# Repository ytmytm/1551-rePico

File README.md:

# 1551-rePico

Commodore **1551** disk-drive replacement for **Plus/4 / C16 / C116**, based on a [Raspberry Pi Pico 2](https://www.raspberrypi.com/products/raspberry-pi-pico-2/) (RP2350, **non-wireless** — raspberry logo on the soldermask; not Pico 2 W). Firmware and GCR/SD logic are derived from [1541-rePico](https://github.com/fook42/1541-rePico) / [1541-rebuild](https://github.com/ThKattanek/1541-rebuild).

## What this is

A self-contained **drive computer** — **Pico 2** + **6510T** (or [MOS CPU Replacer](https://github.com/monotech/MOS_CPU_Replacer)) + XC9572XL CPLD + RAM + ROM — that replaces the Pi1551-III mainboard (Raspberry Pi 3 + TCBM). It reuses the Pi1551-III **mechanical stack**: front panel, top/bottom faceplates, and overall assembly. BOM, Gerbers, and build notes for those parts stay in the [Pi1551-III](https://github.com/ytmytm/Pi1551-III) repository.

The finished device connects to the computer through a ribbon cable to **[plus4-tcbm2sd](https://github.com/ytmytm/plus4-tcbm2sd)** — same as Pi1551-III.

In short: same case and front panel as Pi1551-III; this repo supplies the Pico 2 / 6510T mainboard, CPLD bitstream, DOS ROMs, and firmware.

### Repository layout

| Path | Role |
|------|------|
| `firmware-1551-III-pico/` | **Supported** firmware |
| `hardware-1551-III-Pico/` | **Supported** KiCad mainboard |
| `hdl-1551-III/` | **Supported** CPLD (`Fake6523`) |
| `roms/` | **Supported** 1551 DOS images for the 27C512 (see [`roms/README.md`](roms/README.md)) |
| `no-OS-FatFS-SD-SDIO-SPI-RPi-Pico/` | Shared FatFs/SD submodule |
| `tools/` | Optional host helper (`conv_x64` D64↔G64); see [`tools/README.md`](tools/README.md) |
| `experimental/` | **Archival only** — early plug-over-1551 daughterboard + old firmware (see [`experimental/README.md`](experimental/README.md)) |

### Compared to a stock 1551

| Stock 1551 | This board |
|------------|------------|
| **6510T** CPU | Same **6510T**, or a [MOS CPU Replacer](https://github.com/monotech/MOS_CPU_Replacer) in that socket |
| ~2 KB SRAM | **32 KB** SRAM (`KM62256`) with a **1551-RAMBoard-style** map: `$0000–$3FFF` + `$8000–$9FFF` (extra RAM window; decode in the CPLD) |
| ~16 KB ROM | **64 KB** EPROM (`27C512`): two **32 KB** DOS images, selected by jumper **J2** — burn a [1551-RAMBOard](https://github.com/ytmytm/1551-RAMBOard) 64K image from [`roms/`](roms/) |
| Device #8 / #9 (hardware strap) | Jumper / strap for **device 8 or 9** (same idea as stock) |
| **6523** TPI + discrete address decode | **XC9572XL CPLD** (`hdl-1551-III/` Fake6523): TPI replacement **and** RAM/ROM chip-select decode |
| 2 MHz crystal (Phi0) | **Pico 2** generates **2 MHz Phi0** (PWM) |
| ~100 Hz IRQ oscillator | **Pico 2** generates **100 Hz IRQ** (PWM) |
| Analog floppy + mech | **Pico 2** emulates the analog path and runs the UI |

### Pico 2 on this board

- **Phi0** and **IRQ** as in the table above — those clocks take dedicated GPIOs that a stock gate-array / discrete oscillator would otherwise free up
- Supplies **3.3 V** for the CPLD (and other 3.3 V rails on this board)
- Front-panel **UI**: OLED (I2C), plus rotary encoder, Back/Insert, SD card-detect, and DS0/DS1 via a **74HCT165** (same panel as Pi1551-III). The '165 is needed because after clock, IRQ, floppy bus, SPI SD, and I2C there were not enough GPIOs for every panel line directly
- **SD card**: FatFs images, browser UI, **card-detect hotplug**
- Floppy **datastream**: GCR to/from the “head”, **BYTE_READY** / related timing
- **Stepper**, optional **density** from DS0/DS1, **WPS** / disk-change toward DOS, activity LED

### CPLD role (short)

Bidirectional **ports** (TCBM on A, head data on B, handshake / MODE / DEVNUM / SYNC on C) are based on [ZXByteman/Fake6523](https://github.com/ZXByteman/Fake6523). The same chip is also **logic glue**:

- RAMBOard-style **address decode** (`/RAMSEL`, `/RAMOE`, `/ROMSEL`, TPI `/CS`), all **PHI2-qualified**
- **`XR/~W`** for SRAM `/WE` (qualified with PHI2)
- **`byte_latched`**: Pico 2 strobes `byte_ready_3v3`; the CPLD latches on the falling edge; any CPU access to the TPI window (`$4000–$7FFF`, e.g. DOS `BIT $4000`) clears the latch — the classic floppy byte-ready behaviour from 1541/1571 service docs, without a dedicated 1551 manual

## What you can do with it

- Mount **D64**, **G64**, and **PRG** images from an SD card (PRG is wrapped on the fly into a temporary D64). Format notes: [D64](doc/D64.TXT), [G64](doc/G64.TXT); optional PC conversion with [`tools/conv_x64`](tools/)
- Browse and mount images from the **OLED + encoder** front panel (Back / Insert), with **SD hotplug** when the socket has a card-detect switch
- Run as device **#8 or #9** on the Plus/4 TCBM bus via **[plus4-tcbm2sd](https://github.com/ytmytm/plus4-tcbm2sd)**
- Use **[1551-RAMBOard](https://github.com/ytmytm/1551-RAMBOard)** patched DOS in the 27C512 so track-cache / HypaRAM-style fastloaders work
- Prefer **[Parobek](https://github.com/ytmytm/plus4-parobek)** as the host utility ROM: it autodetects the RAMBOard DOS patch and provides a fastloader. For now we use Parobek’s **DirectoryBrowser** on the computer; `firmware-1551-III-pico/SoftwareC16/db12b.prg` is kept for a future on-device Load Selector (**TODO**)

## Build and assemble

### 1. Clone (with submodules)

The FatFs/SD driver is a **git submodule**. Without it, CMake will fail.

```bash
git clone --recurse-submodules https://github.com/ytmytm/1551-rePico.git
cd 1551-rePico
```

If you already cloned without submodules:

```bash
git submodule update --init --recursive
```

You need at least `no-OS-FatFS-SD-SDIO-SPI-RPi-Pico/` for the supported firmware.

### 2. Host packages

**Linux (Debian-like):**

```bash
sudo apt install cmake ninja-build libusb-1.0-0-dev build-essential \
  pkg-config python3 xxd gcc-arm-none-eabi \
  libnewlib-arm-none-eabi libstdc++-arm-none-eabi-newlib
```

**macOS (Homebrew):**

```bash
brew install cmake ninja libusb pkg-config python3
brew install --cask gcc-arm-embedded
```

`xxd` is usually already on macOS (Xcode Command Line Tools). Ensure `arm-none-eabi-gcc` is on your `PATH`.

### 3. Raspberry Pi Pico SDK

From [pico-sdk](https://github.com/raspberrypi/pico-sdk):

```bash
git clone https://github.com/raspberrypi/pico-sdk.git
cd pico-sdk
git submodule update --init lib/mbedtls
export PICO_SDK_PATH="$(pwd)"
echo "export PICO_SDK_PATH=$PICO_SDK_PATH" >> ~/.profile
```

Open a new shell (or `source ~/.profile`) so `PICO_SDK_PATH` is set. The Raspberry Pi Pico VS Code extension / `.pico-sdk` can provide the SDK instead.

### 4. picotool

From [picotool](https://github.com/raspberrypi/picotool): clone and build/install as in its README / BUILDING.md so `picotool` is on your `PATH`.

### 5. Compile firmware

```bash
cd firmware-1551-III-pico
mkdir -p build && cd build
cmake -G Ninja -DCMAKE_BUILD_TYPE=Release ..
ninja
```

Outputs include `1551-III-Pico.uf2` and `1551-III-Pico.elf`.

### 6. Flash the Pico 2

```bash
picotool load -t uf2 1551-III-Pico.uf2 -x -f
```

`-f` forces BOOTSEL when the app is running; `-x` starts the new firmware after load.

### 7. Main PCB (order / solder)

KiCad project: [`hardware-1551-III-Pico/`](hardware-1551-III-Pico/) (see its [`README.md`](hardware-1551-III-Pico/README.md)).

- Schematic PDF: [`plots/1551-III-Pico.pdf`](hardware-1551-III-Pico/plots/1551-III-Pico.pdf)
- Gerbers / drills: [`plots/`](hardware-1551-III-Pico/plots/)
- Fab pack: [`production/1551-III_Pico_2b.zip`](hardware-1551-III-Pico/production/1551-III_Pico_2b.zip)
- BOM / pick-and-place: [`production/bom.csv`](hardware-1551-III-Pico/production/bom.csv), [`positions.csv`](hardware-1551-III-Pico/production/positions.csv), [`designators.csv`](hardware-1551-III-Pico/production/designators.csv)
- **JP1–JP3**: leave default **1–2** (Pico 2 ↔ `74HCT165`). Alternate wiring was only insurance if the shift register failed — do not change them.

### 8. Program the CPLD

Flash [`hdl-1551-III/Fake6523.jed`](hdl-1551-III/Fake6523.jed) into the XC9572XL. The `.jed` was built with [Xilinx ISE 14.7](https://www.xilinx.com/support/download/index.html/content/xilinx/en/downloadNav/vivado-design-tools/archive-ise.html) (sources in `hdl-1551-III/`). Rebuild and JTAG steps (a Raspberry Pi 3 and jumper wires are enough) are in [plus4-tcbm2sd → CPLD firmware](https://github.com/ytmytm/plus4-tcbm2sd/blob/main/HardwareFirmware.md#cpld-firmware); the procedure is the same for this board.

### 9. Burn the DOS ROM

Program a 64K image from [`roms/`](roms/) into the 27C512 (see [`roms/README.md`](roms/README.md)). Prefer a [1551-RAMBOard](https://github.com/ytmytm/1551-RAMBOard) image; jumper **J2** selects the active 32K half (use the patched upper bank).

### 10. Panel, case, and host link

- Front panel / faceplates / mechanical assembly: **[Pi1551-III](https://github.com/ytmytm/Pi1551-III)**
- Host: **[plus4-tcbm2sd](https://github.com/ytmytm/plus4-tcbm2sd)** + ribbon cable

## History and relation to 1541-rePico

This is a **separate product**, not a fork kept in sync with upstream 1541-rePico: a real **6510T** + CPLD 1551 path in a [Pi1551-III](https://github.com/ytmytm/Pi1551-III) enclosure. Useful upstream changes may still be cherry-picked by hand.

**Starting point.** Take 1541-rePico’s GCR/SD/UI core and aim at a **1551** for Plus/4 that still fits **Pi1551-III** and talks through **tcbm2sd**, so the Pi 3 Module-rotated board becomes a Pico 2 + real 6510T path.

**Daughterboard bring-up** (now `experimental/`). First hardware plugged over a stock 1551 mainboard: reuse CPU/TPI/RAM/ROM, Pico 2 for the analog path, Fake6523 in the CPLD. That proved TCBM/GCR, pin maps, and design rules: Phi0 and 100 Hz IRQ from the Pico 2 (gate array optional), `XR/~W` in the CPLD, PHI2-qualified chip-selects (otherwise RAM bus contention), `byte_latched` as classic byte-ready, and slower zone-0 timing than 1541 defaults. Once the motherboard was only a RAM/ROM carrier, a self-contained board was the next step.

**1551-III-Pico.** Decode moved into the CPLD (no discrete `'139`/`'00`), RAMBOard map and 64K DOS images, Pi1551-III panel (SH1106 + 74HCT165). Firmware lives in `firmware-1551-III-pico/`. Upstream 1541-rePico is not merged as a whole — only occasional hand cherry-picks.

| Mostly from 1541-rePico | Mostly new for 1551 / this board |
|-------------------------|----------------------------------|
| GCR encode/decode, track buffers, D64/G64 path | KiCad III board, CPLD glue + Fake6523 ports, RAMBOard decode |
| FatFs / SD wiring, much of the menu framework | Pico 2 as Phi0 + 100 Hz IRQ; '165 panel inputs |
| Build/flash with pico-sdk / picotool | TCBM via tcbm2sd; Parobek + patched DOS ROMs |
| | Zone-0 timing, byte-ready latch model, SD hotplug, III pinout |

### Credits

- [1541-rebuild](https://github.com/ThKattanek/1541-rebuild) — Thorsten Kattanek  
- [1541-rePico](https://github.com/fook42/1541-rePico) — fook42 (GCR/SD/UI lineage)  
- C64 image selector in upstream 1541-rePico — Peiselulli  
- Dev-container / debug docs on upstream — [BensonRSI](https://github.com/BensonRSI)  
- [Fake6523](https://github.com/ZXByteman/Fake6523) — ZXByteman / go4retro  
- [Pi1551-III](https://github.com/ytmytm/Pi1551-III), [plus4-tcbm2sd](https://github.com/ytmytm/plus4-tcbm2sd), [1551-RAMBOard](https://github.com/ytmytm/1551-RAMBOard), [plus4-parobek](https://github.com/ytmytm/plus4-parobek)

## Links

- Disk image formats overview: <https://ist.uwaterloo.ca/~schepers/formats.html>
- forum64 thread behind 1541-rebuild / 1541-rePico: <https://www.forum64.de/index.php?thread/59884-laufwerk-der-1541-emulieren>

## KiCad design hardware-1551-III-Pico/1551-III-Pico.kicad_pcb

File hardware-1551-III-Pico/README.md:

# 1551-III-Pico mainboard

KiCad project for the **horizontal main module** of [1551-rePico](../README.md): Pico2 + 6510T (or [MOS CPU Replacer](https://github.com/monotech/MOS_CPU_Replacer)) + XC9572XL CPLD + 32 KB SRAM + 64 KB EPROM. It replaces the Pi1551-III **Module-rotated** board and mates with the [Pi1551-III](https://github.com/ytmytm/Pi1551-III) front panel and faceplates.

Host connection is a ribbon cable to **[plus4-tcbm2sd](https://github.com/ytmytm/plus4-tcbm2sd)** (same as Pi1551-III).

## Design files

| Artifact | Path |
|----------|------|
| KiCad project | this folder (`1551-III-Pico.kicad_pro`) |
| Schematic PDF | [`plots/1551-III-Pico.pdf`](plots/1551-III-Pico.pdf) |
| Gerbers / drills | [`plots/`](plots/) |
| JLCPCB-style fab pack | [`production/1551-III_Pico_2b.zip`](production/1551-III_Pico_2b.zip) |
| BOM / positions | [`production/bom.csv`](production/bom.csv), [`production/positions.csv`](production/positions.csv), [`production/designators.csv`](production/designators.csv) |

## Related firmware / CPLD / ROMs

- Firmware: [`../firmware-1551-III-pico/`](../firmware-1551-III-pico/)
- CPLD bitstream: [`../hdl-1551-III/Fake6523.jed`](../hdl-1551-III/Fake6523.jed) — flash notes in the [top-level README](../README.md#8-program-the-cpld)
- DOS EPROM images (27C512): [`../roms/`](../roms/) — see [1551-RAMBOard](https://github.com/ytmytm/1551-RAMBOard) for provenance and patch details
- Mechanical / panel BOM: **[Pi1551-III](https://github.com/ytmytm/Pi1551-III)**

## Notes

- Internal bring-up / review notes: [`notes.txt`](notes.txt), [`hardware-review.md`](hardware-review.md)
- ROM bank select on this board is jumper **J2** (two 32 KB halves of the 27C512). Prefer a [1551-RAMBOard](https://github.com/ytmytm/1551-RAMBOard) 64K image so the upper half is the RAM-expansion / fastloader patch.
- **JP1–JP3** (GPIO26–28 ↔ `74HCT165`): leave as shipped / default **1–2**. They were only a fallback so the Pico could talk to the front-panel encoder directly if the shift register failed; '165 works and current firmware expects that path — do not rewire them.

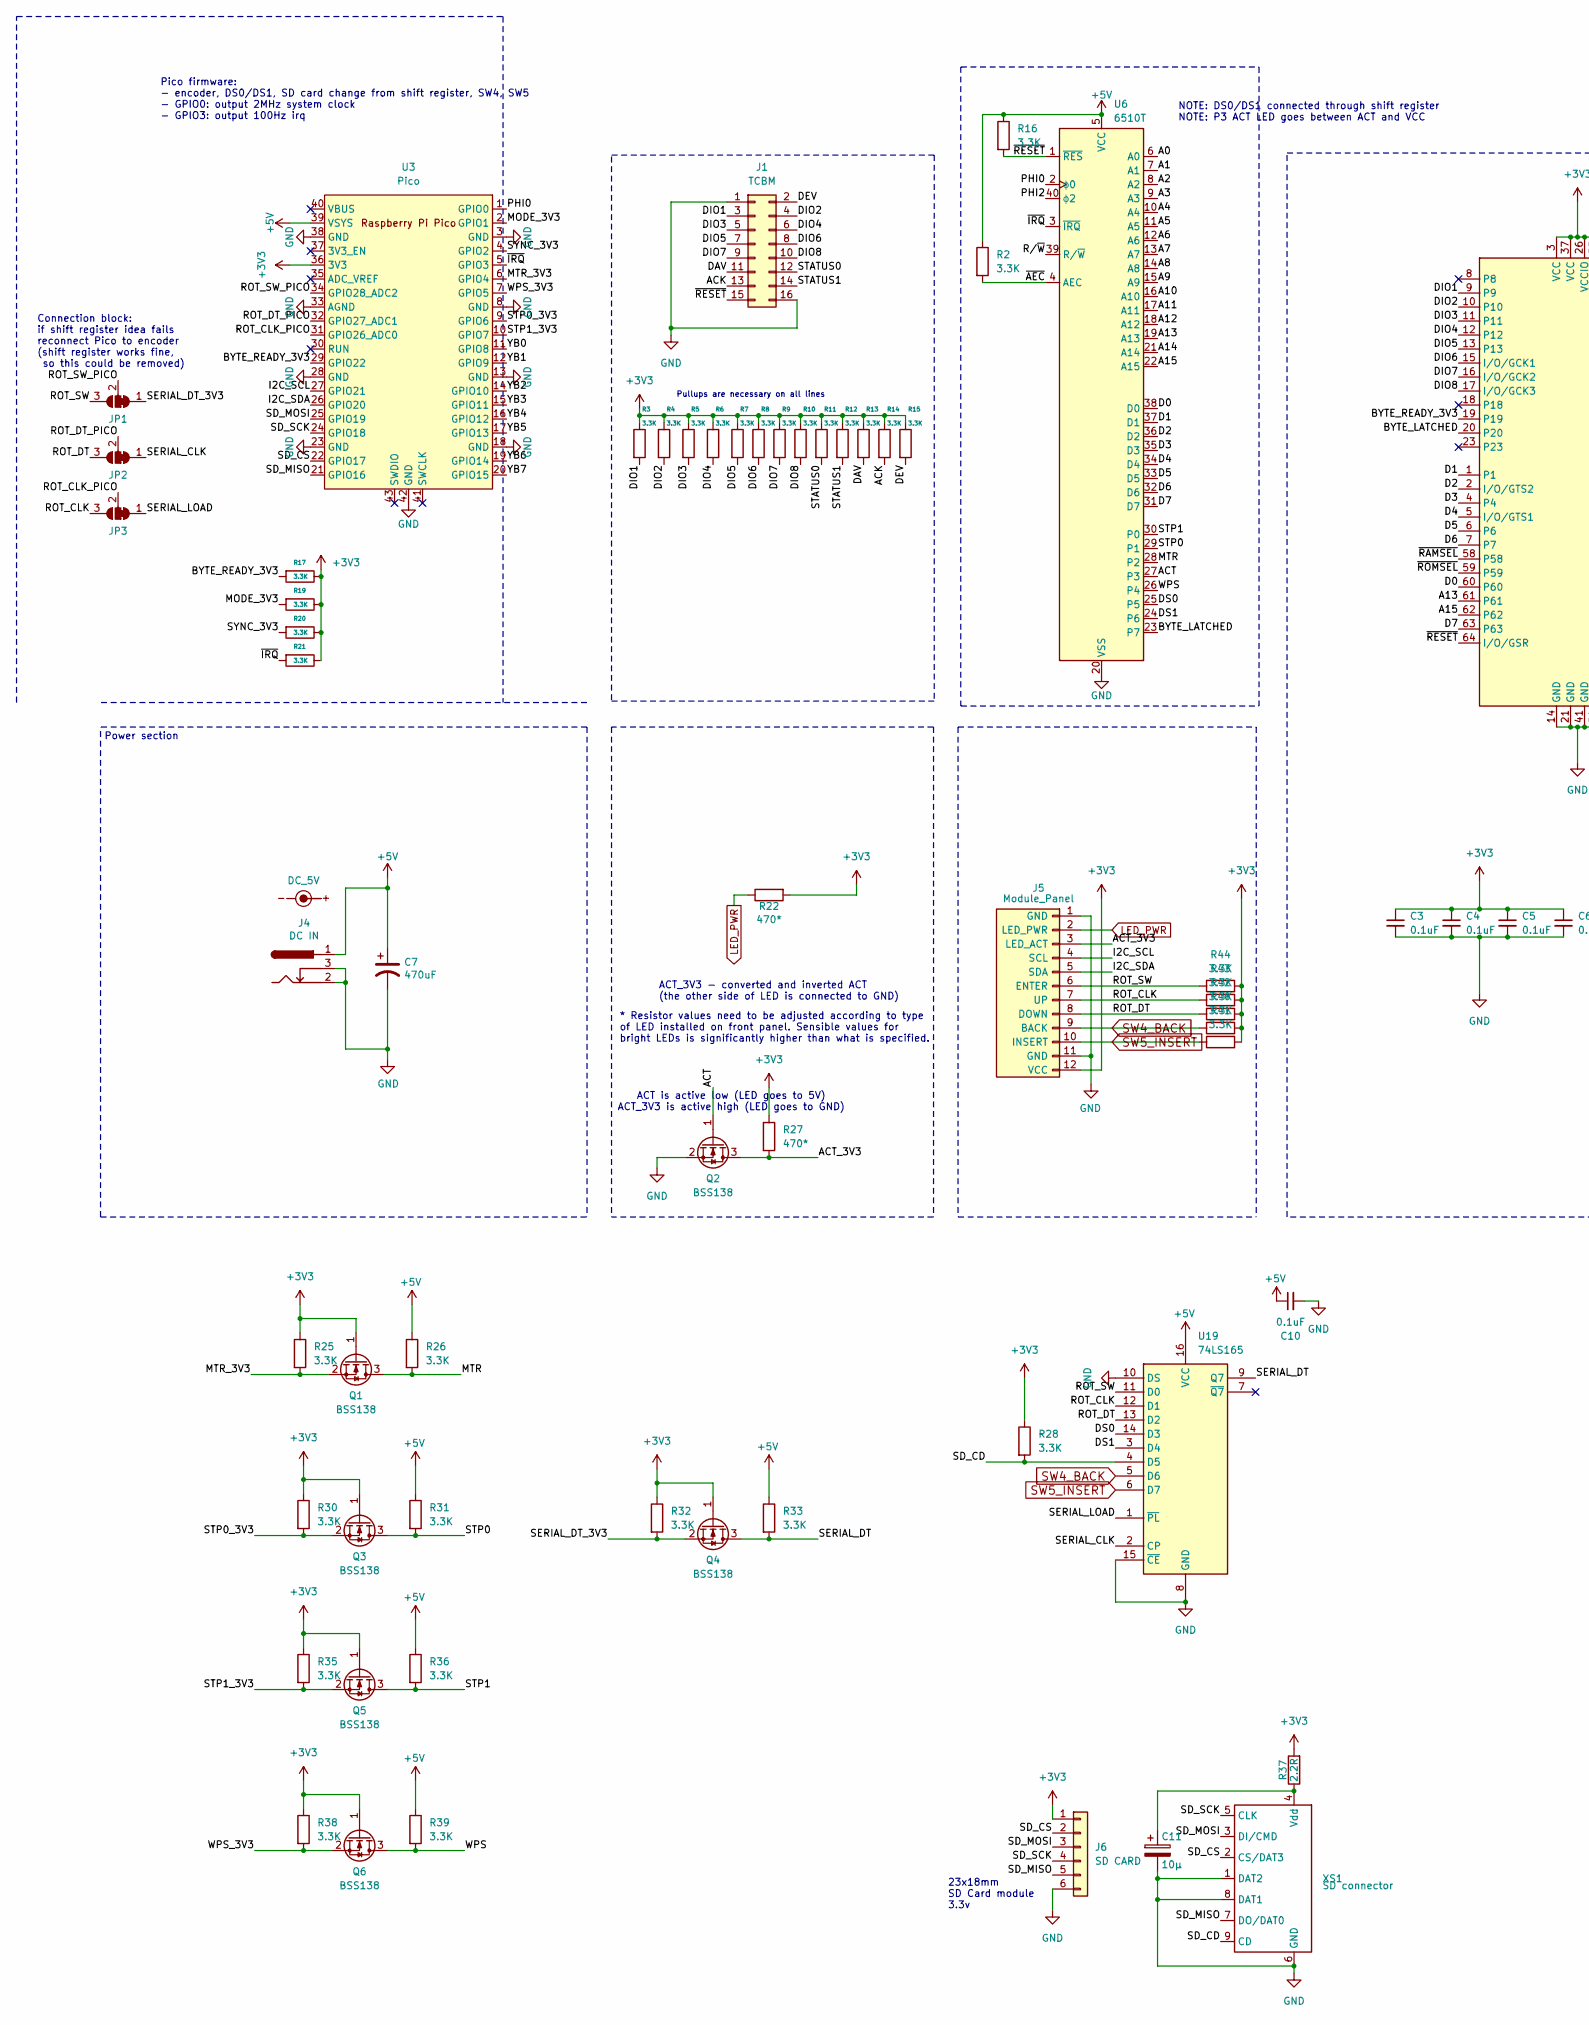
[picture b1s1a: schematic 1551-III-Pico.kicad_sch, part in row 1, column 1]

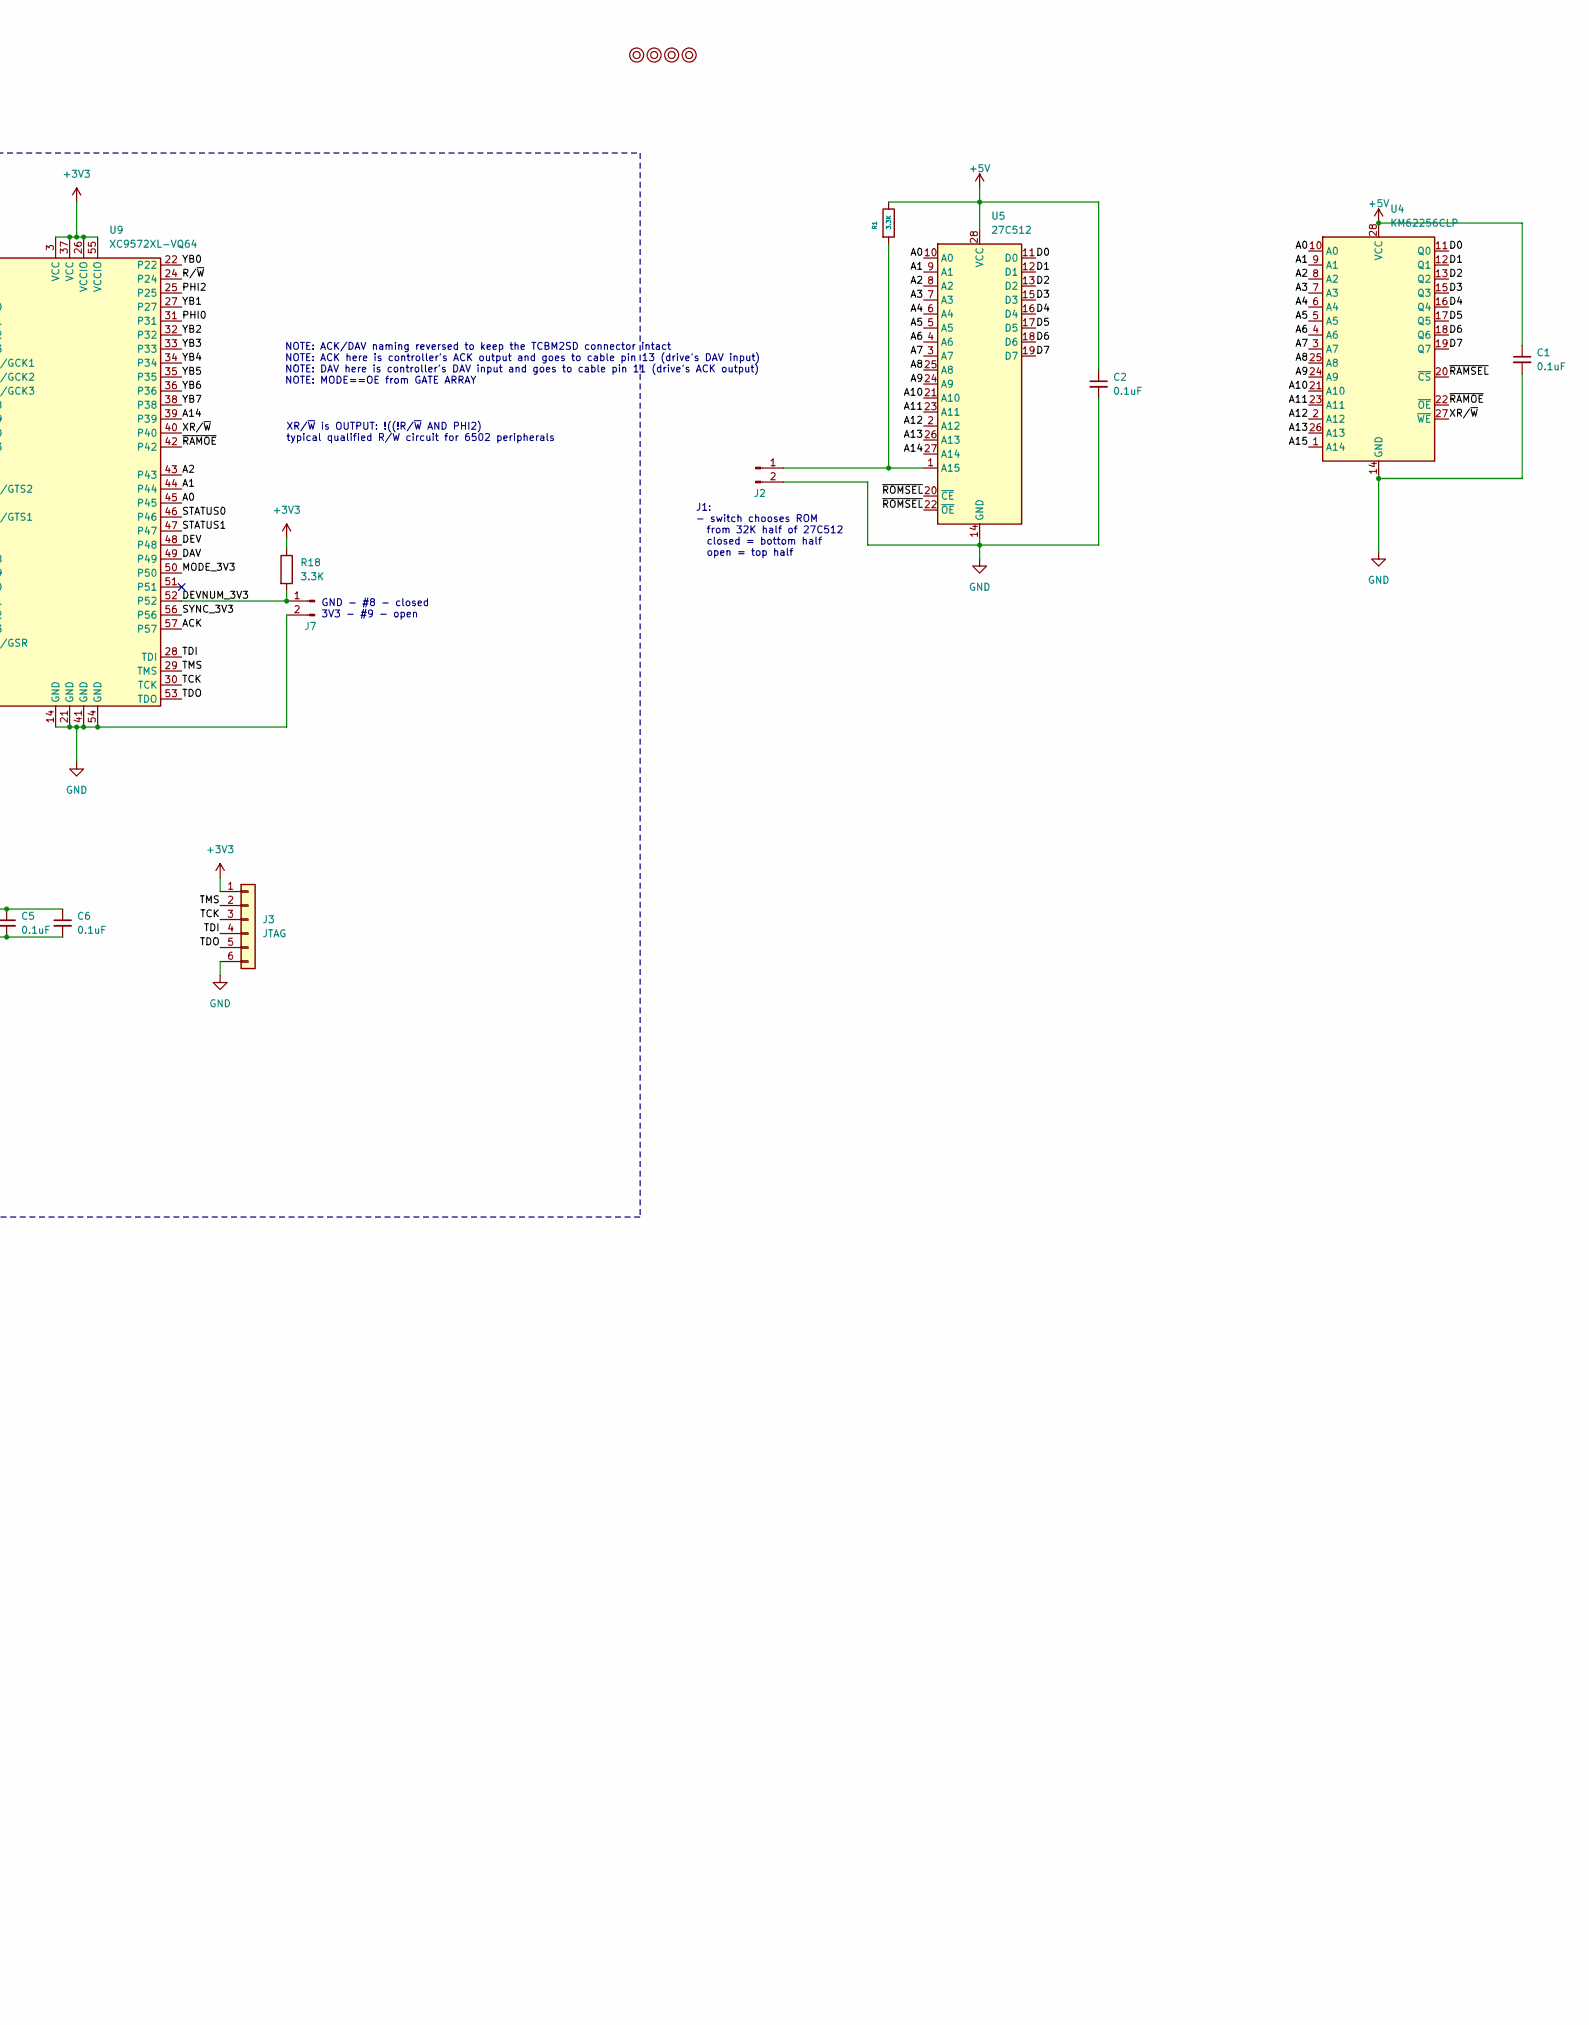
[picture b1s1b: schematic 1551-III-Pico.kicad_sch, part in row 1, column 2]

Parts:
C1, C2, C3, C4, C5, C6, C10: 0.1uF; C_0805_2012Metric_Pad1.18x1.45mm_HandSolder; JLCPCB Part # C49678
C7: 470uF; CP_Radial_D8.0mm_P3.50mm
C11: 10µ; CP_EIA-3216-12_Kemet-S_HandSolder; JLCPCB Part # C1969735
J1: TCBM; IDC-Header_2x08_P2.54mm_Vertical
J2, J7: Conn_01x02_Pin; PinHeader_1x02_P2.54mm_Vertical
J3: JTAG; PinHeader_1x06_P2.54mm_Vertical
J4: DC IN; BARREL_JACK
J5: Module_Panel
J6: SD CARD; PinHeader_1x06_P2.54mm_Vertical
JP1, JP2, JP3: SolderJumper_3_Bridged12; SolderJumper-3_P1.3mm_Bridged12_RoundedPad1.0x1.5mm_NumberL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
M1, M2, M3, M4: Mounting; M3
Q1, Q2, Q3, Q4, Q5, Q6: BSS138; SOT-23; MFR.Part # BSS138; JLCPCB Part # C78284
R1, R2, R3, R4, R5, R6, R7, R8, R9, R10, R11, R12, R13, R14, R15, R16, R17, R18, R19, R20, R21, R25, R26, R28, R30, R31, R32, R33, R35, R36, R38, R39, R40, R41, R42, R43, R44: 3.3K; R_0805_2012Metric_Pad1.20x1.40mm_HandSolder; MFR.Part # 0805W8F3301T5E; JLCPCB Part # C26010
R22, R27: 470*; R_0805_2012Metric_Pad1.20x1.40mm_HandSolder; MFR.Part # 0805W8F4700T5E; JLCPCB Part # C17710
R37: 2.2R; R_0805_2012Metric_Pad1.20x1.40mm_HandSolder; JLCPCB Part # C17521
SYM1: DC_5V; PWR_Specification
U3: Pico; RPi_Pico_SMD_TH
U4: KM62256CLP; DIP-28_W15.24mm_Socket_LongPads
U5: 27C512; DIP-28_W15.24mm_Socket_LongPads
U6: 6510T; DIP-40_W15.24mm
U9: XC9572XL-VQ64; TQFP-64_10x10mm_P0.5mm; JLCPCB Part # C90569
U19: 74LS165; SOP-16_4.4x10.4mm_P1.27mm; MFR.Part # SN74LS165ADR; JLCPCB Part # C7742
XS1: SD connector; Conn_uSDcard; JLCPCB Part # C7529389

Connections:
+3V3: C3.1, C4.1, C5.1, C6.1, J3.1, J5.12 (VCC), J6.1, Q1.1 (G), Q3.1 (G), Q4.1 (G), Q5.1 (G), Q6.1 (G), R3.1, R4.1, R5.1, R6.1, R7.1, R8.1, R9.1, R10.1, R11.1, R12.1, R13.1, R14.1, R15.1, R17.1, R18.1, R19.1, R20.1, R21.1, R22.2, R25.1, R27.1, R28.1, R30.1, R32.1, R35.1, R37.2, R38.1, R40.2, R41.2, R42.2, R43.2, R44.2, U3.36 (3V3), U9.3 (VCC), U9.26 (VCCIO), U9.37 (VCC), U9.55 (VCCIO)
+5V: C1.1, C2.1, C7.1, C10.1, J4.1, R1.1, R2.1, R16.1, R26.1, R31.1, R33.1, R36.1, R39.1, U3.39 (VSYS), U4.28 (VCC), U5.28 (VCC), U6.5 (VCC), U19.16 (VCC)
/A0: U4.10 (A0), U5.10 (A0), U6.6 (A0), U9.45
/A1: U4.9 (A1), U5.9 (A1), U6.7 (A1), U9.44
/A2: U4.8 (A2), U5.8 (A2), U6.8 (A2), U9.43
/A3: U4.7 (A3), U5.7 (A3), U6.9 (A3)
/A4: U4.6 (A4), U5.6 (A4), U6.10 (A4)
/A5: U4.5 (A5), U5.5 (A5), U6.11 (A5)
/A6: U4.4 (A6), U5.4 (A6), U6.12 (A6)
/A7: U4.3 (A7), U5.3 (A7), U6.13 (A7)
/A8: U4.25 (A8), U5.25 (A8), U6.14 (A8)
/A9: U4.24 (A9), U5.24 (A9), U6.15 (A9)
/A10: U4.21 (A10), U5.21 (A10), U6.16 (A10)
/A11: U4.23 (A11), U5.23 (A11), U6.17 (A11)
/A12: U4.2 (A12), U5.2 (A12), U6.18 (A12)
/A13: U4.26 (A13), U5.26 (A13), U6.19 (A13), U9.61
/A14: U5.27 (A14), U6.21 (A14), U9.39
/A15: U4.1 (A14), U6.22 (A15), U9.62
/ACK: J1.13, R14.2, U9.57
/ACT: Q2.1 (G), U6.27 (P3)
/ACT_3V3: J5.3 (LED_ACT), Q2.3 (D), R27.2
/BYTE_LATCHED: U6.23 (P7), U9.20
/BYTE_READY_3V3: R17.2, U3.29 (GPIO22), U9.19
/D0: U4.11 (Q0), U5.11 (D0), U6.38 (D0), U9.60
/D1: U4.12 (Q1), U5.12 (D1), U6.37 (D1), U9.1
/D2: U4.13 (Q2), U5.13 (D2), U6.36 (D2), U9.2 (I/O/GTS2)
/D3: U4.15 (Q3), U5.15 (D3), U6.35 (D3), U9.4
/D4: U4.16 (Q4), U5.16 (D4), U6.34 (D4), U9.5 (I/O/GTS1)
/D5: U4.17 (Q5), U5.17 (D5), U6.33 (D5), U9.6
/D6: U4.18 (Q6), U5.18 (D6), U6.32 (D6), U9.7
/D7: U4.19 (Q7), U5.19 (D7), U6.31 (D7), U9.63
/DAV: J1.11, R13.2, U9.49
/DEV: J1.2, R15.2, U9.48
/DEVNUM_3V3: J7.1, R18.2, U9.52
/DIO1: J1.3, R3.2, U9.9
/DIO2: J1.4, R4.2, U9.10
/DIO3: J1.5, R5.2, U9.11
/DIO4: J1.6, R6.2, U9.12
/DIO5: J1.7, R7.2, U9.13
/DIO6: J1.8, R8.2, U9.15 (I/O/GCK1)
/DIO7: J1.9, R9.2, U9.16 (I/O/GCK2)
/DIO8: J1.10, R10.2, U9.17 (I/O/GCK3)
/DS0: U6.25 (P5), U19.14 (D3)
/DS1: U6.24 (P6), U19.3 (D4)
/I2C_SCL: J5.4 (SCL), U3.27 (GPIO21)
/I2C_SDA: J5.5 (SDA), U3.26 (GPIO20)
/MODE_3V3: R19.2, U3.2 (GPIO1), U9.50
/MTR: Q1.3 (D), R26.2, U6.28 (P2)
/MTR_3V3: Q1.2 (S), R25.2, U3.6 (GPIO4)
/PHI0: U3.1 (GPIO0), U6.2 (ϕ0), U9.31
/PHI2: U6.40 (ϕ2), U9.25
/ROT_CLK: J5.7 (UP), JP3.3 (B), R43.1, U19.12 (D1)
/ROT_CLK_PICO: JP3.2 (C), U3.31 (GPIO26_ADC0)
/ROT_DT: J5.8 (DOWN), JP2.3 (B), R42.1, U19.13 (D2)
/ROT_DT_PICO: JP2.2 (C), U3.32 (GPIO27_ADC1)
/ROT_SW: J5.6 (ENTER), JP1.3 (B), R44.1, U19.11 (D0)
/ROT_SW_PICO: JP1.2 (C), U3.34 (GPIO28_ADC2)
/R/~W: U6.39 (R/~W), U9.24
/SD_CD: R28.2, U19.4 (D5), XS1.9 (CD)
/SD_CS: J6.2, U3.22 (GPIO17), XS1.2 (CS/DAT3)
/SD_MISO: J6.5, U3.21 (GPIO16), XS1.7 (DO/DAT0)
/SD_MOSI: J6.3, U3.25 (GPIO19), XS1.3 (DI/CMD)
/SD_SCK: J6.4, U3.24 (GPIO18), XS1.5 (CLK)
/SERIAL_CLK: JP2.1 (A), U19.2 (CP)
/SERIAL_DT: Q4.3 (D), R33.2, U19.9 (Q7)
/SERIAL_DT_3V3: JP1.1 (A), Q4.2 (S), R32.2
/SERIAL_LOAD: JP3.1 (A), U19.1 (~PL)
/STATUS0: J1.12, R11.2, U9.46
/STATUS1: J1.14, R12.2, U9.47
/STP0: Q3.3 (D), R31.2, U6.29 (P1)
/STP0_3V3: Q3.2 (S), R30.2, U3.9 (GPIO6)
/STP1: Q5.3 (D), R36.2, U6.30 (P0)
/STP1_3V3: Q5.2 (S), R35.2, U3.10 (GPIO7)
/SYNC_3V3: R20.2, U3.4 (GPIO2), U9.56
/TCK: J3.3, U9.30 (TCK)
/TDI: J3.4, U9.28 (TDI)
/TDO: J3.5, U9.53 (TDO)
/TMS: J3.2, U9.29 (TMS)
/WPS: Q6.3 (D), R39.2, U6.26 (P4)
/WPS_3V3: Q6.2 (S), R38.2, U3.7 (GPIO5)
/XR/~W: U4.27 (~WE), U9.40
/YB0: U3.11 (GPIO8), U9.22
/YB1: U3.12 (GPIO9), U9.27
/YB2: U3.14 (GPIO10), U9.32
/YB3: U3.15 (GPIO11), U9.33
/YB4: U3.16 (GPIO12), U9.34
/YB5: U3.17 (GPIO13), U9.35
/YB6: U3.19 (GPIO14), U9.36
/YB7: U3.20 (GPIO15), U9.38
/~AEC: R2.2, U6.4 (AEC)
/~IRQ: R21.2, U3.5 (GPIO3), U6.3 (~IRQ)
/~RAMOE: U4.22 (~OE), U9.42
/~RAMSEL: U4.20 (~CS), U9.58
/~RESET: J1.15, R16.2, U6.1 (~RES), U9.64 (I/O/GSR)
/~ROMSEL: U5.20 (~CE), U5.22 (~OE), U9.59
GND: C1.2, C2.2, C3.2, C4.2, C5.2, C6.2, C7.2, C10.2, C11.2, J1.1, J1.16, J2.2, J3.6, J4.2, J4.3, J5.1 (GND), J5.11 (GND), J6.6, J7.2, Q2.2 (S), U3.3 (GND), U3.8 (GND), U3.13 (GND), U3.18 (GND), U3.23 (GND), U3.28 (GND), U3.33 (AGND), U3.38 (GND), U3.42 (GND), U4.14 (GND), U5.14 (GND), U6.20 (VSS), U9.14 (GND), U9.21 (GND), U9.41 (GND), U9.54 (GND), U19.8 (GND), U19.10 (DS), U19.15 (~CE), XS1.1 (DAT2), XS1.6 (GND), XS1.8 (DAT1)
LED_PWR: J5.2 (LED_PWR), R22.1
unnamed: J2.1, R1.2, U5.1 (A15)
unnamed: C11.1, R37.1, XS1.4 (Vdd)
SW4_BACK: J5.9 (BACK), R40.1, U19.5 (D6)
SW5_INSERT: J5.10 (INSERT), R41.1, U19.6 (D7)

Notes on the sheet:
Pico firmware: - encoder, DS0/DS1, SD card change from shift register, SW4, SW5 - GPIO0: output 2MHz system clock - GPIO3: output 100Hz irq
Pullups are necessary on all lines
J1: - switch chooses ROM from 32K half of 27C512 closed = bottom half open = top half
Connection block: if shift register idea fails reconnect Pico to encoder (shift register works fine, so this could be removed)
* Resistor values need to be adjusted according to type of LED installed on front panel. Sensible values for bright LEDs is significantly higher than what is specified.
XR/~{W} is OUTPUT: !((!R/~{W} AND PHI2) typical qualified R/W circuit for 6502 peripherals
ACT_3V3 - converted and inverted ACT (the other side of LED is connected to GND)
23x18mm SD Card module 3.3v
ACT is active low (LED goes to 5V) ACT_3V3 is active high (LED goes to GND)
Power section
NOTE: ACK/DAV naming reversed to keep the TCBM2SD connector intact NOTE: ACK here is controller's ACK output and goes to cable pin 13 (drive's DAV input) NOTE: DAV here is controller's DAV input and goes to cable pin 11 (drive's ACK output) NOTE: MODE==OE from GATE ARRAY
GND - #8 - closed 3V3 - #9 - open
NOTE: DS0/DS1 connected through shift register NOTE: P3 ACT LED goes between ACT and VCC

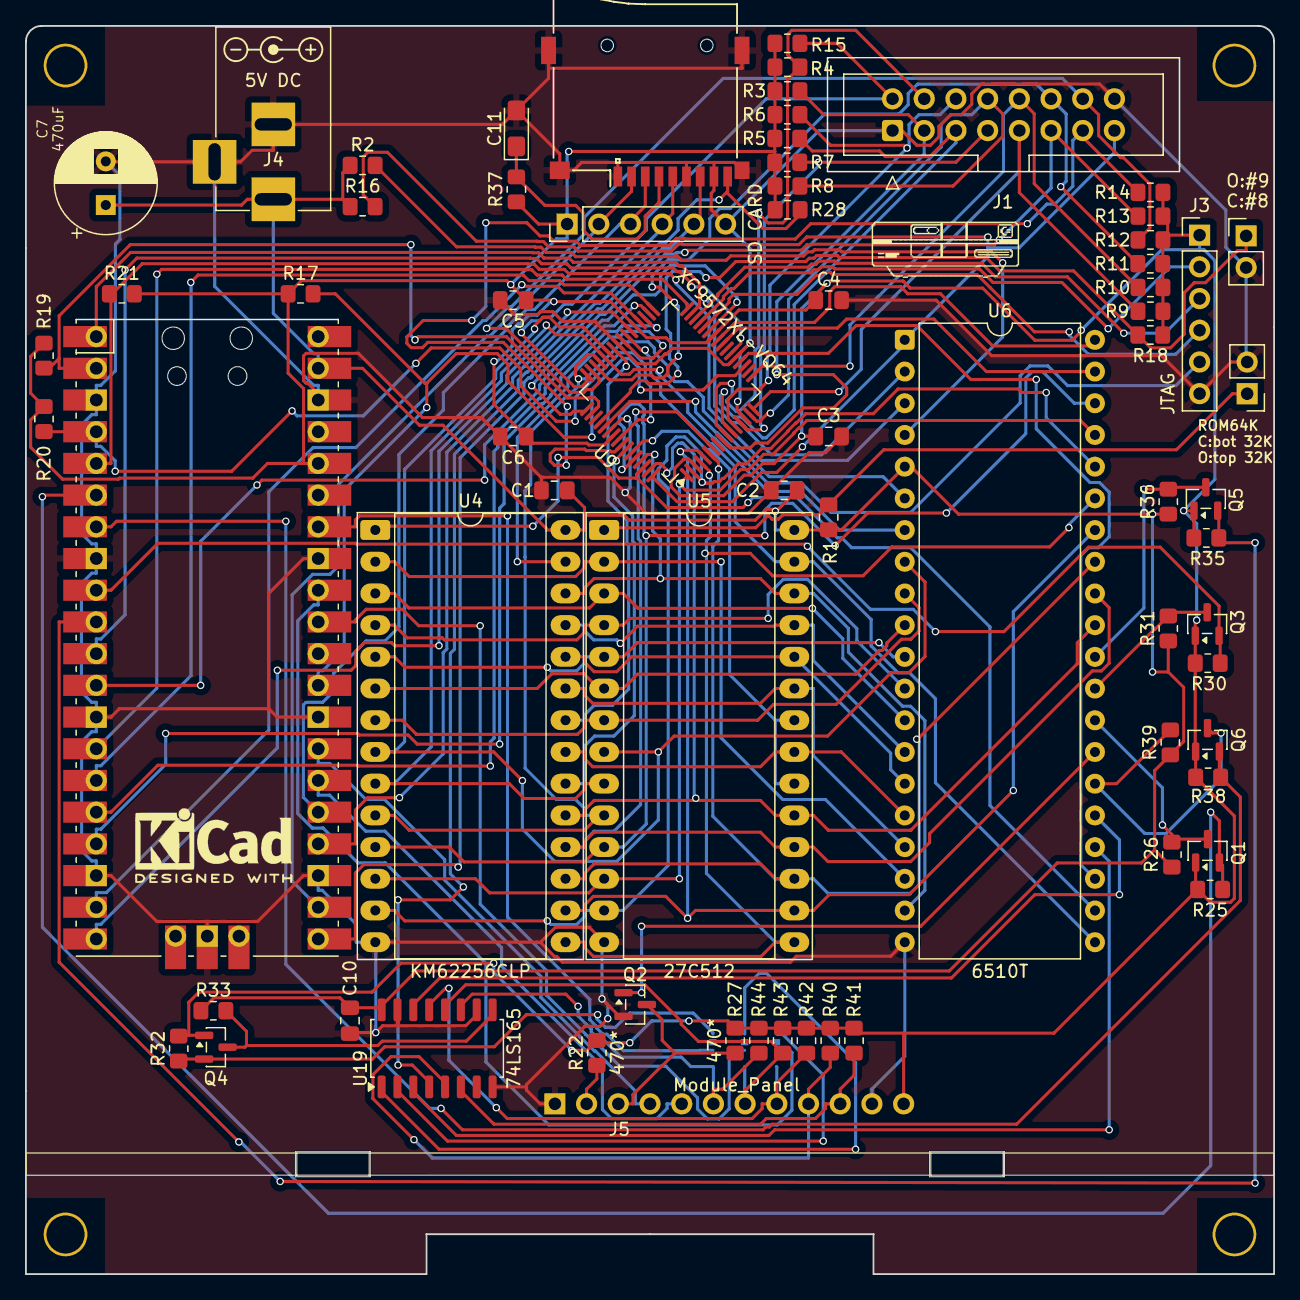
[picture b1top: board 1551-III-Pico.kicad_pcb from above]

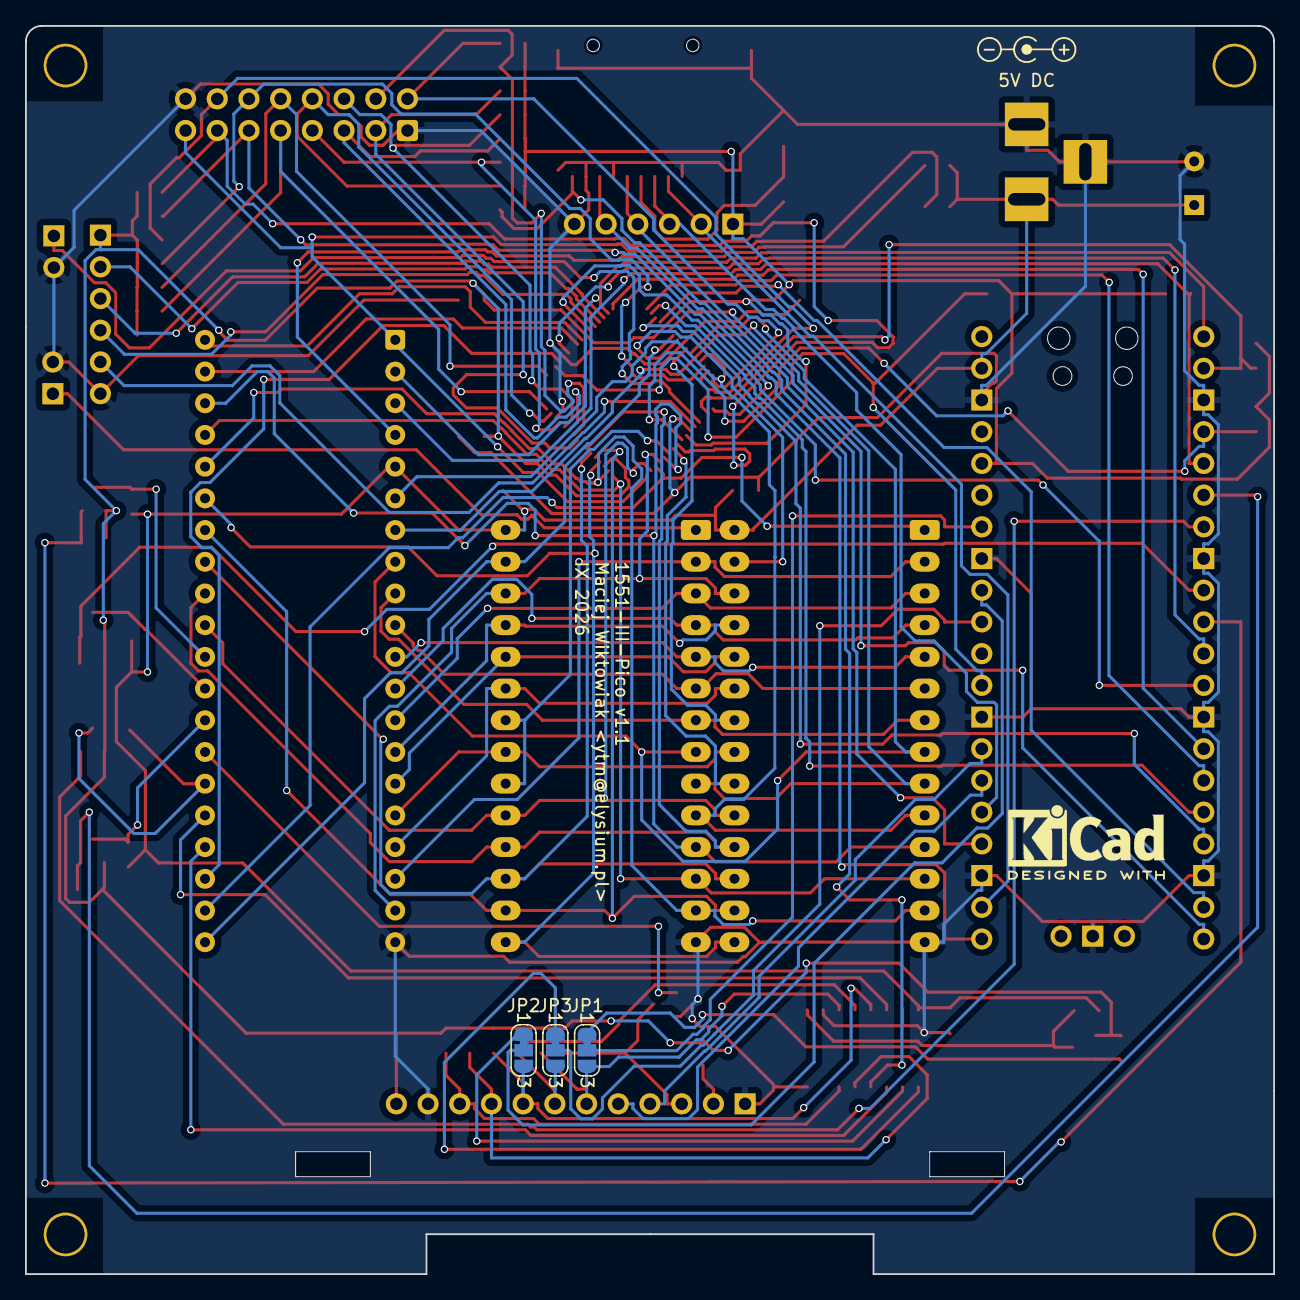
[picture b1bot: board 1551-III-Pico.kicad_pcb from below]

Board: 2 copper layers, 100.0 x 100.0 mm, 80 parts (4 on the bottom side), 101 nets.

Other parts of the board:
Pi1541-drive: Pi1541-drive
REF1, REF2: KiCad-Logo2_6mm_SilkScreen

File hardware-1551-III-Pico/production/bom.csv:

Designator,Footprint,Quantity,Value,LCSC Part #
"C1, C10, C2, C3, C4, C5, C6",0805,7,0.1uF,C49678
C11,CP_EIA-3216-12_Kemet-S_HandSolder,1,10µ,C1969735
"Q1, Q2, Q3, Q4, Q5, Q6",SOT-23,6,BSS138,C78284
"R1, R10, R11, R12, R13, R14, R15, R16, R17, R18, R19, R2, R20, R21, R25, R26, R28, R3, R30, R31, R32, R33, R35, R36, R38, R39, R4, R40, R41, R42, R43, R44, R5, R6, R7, R8, R9",0805,37,3.3K,C26010
"R22, R27",0805,2,470*,C17710
R37,0805,1,2.2R,C17521
U19,SOP-16_4.4x10.4mm_P1.27mm,1,74LS165,C7742
U9,TQFP-64_10x10mm_P0.5mm,1,XC9572XL-VQ64,C90569
XS1,Conn_uSDcard,1,SD connector,C7529389
